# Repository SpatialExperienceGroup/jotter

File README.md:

# Jotter

## Requirements
- micro usb port for charging and for updating firmware
- 3.7V from a lipo battery
- lipo charging circuitry through a micro usb port
- bluetooth low energy beacon receiver and transmitter for positioning and ideally multilateration
- MCU to handle bluetooth beacon code
- accurate real time clock
- sd card for storing data; consider storing the unit id number on the sd card
- mems microphone on front for capturing talking of others
- mems microphone on the back for capturing talking of user
- MCU for DFT processing of the audio signals
- IrDA or similar for transmitting and receiving unique IDs to identify users facing users
- MCU to handing IrDA
- accelerometer to identify leaning and sitting
- pressure sensor to identify sitting and standing, usually these are only accurate to within 1 meter, which might not be good enough
- Wi-Fi capability for updating firmware, changing settings, and downloading data
- Any LEDs? charging, Wi-Fi transmission
- Any Buttons? Wi-Fi mode

---------------
## RTC
### DS3231*
- Arduino Library: Rtc by Makuna, Sodaq_DS3231

#### DS3231SN
- has temperature compensated crystal oscillator (may need this for cold temps)
- TCXO:Yes
- Alamrs:2
- $9.97@1, digi-key
- $6.59@100, digi-key
- $2.50@10, aliexpress

---------------
## Coin Cell Retainer/Holder
- Battery:CR2032
- Battery Diameter:20mm

### BU2032

#### BU2032-1-HD-G
- Type:through hole holder
- $0.83@1, digi-key
- $0.69@100, digi-key

#### BU2032SM-HD-G
- Type:surface mount holder
- $0.87@1, digi-key
- $0.76@100, digi-key

#### BK-912
- Type:surface mount retainer
- Notes:easy replacement
- $0.33@1, digi-key
- $0.29@100, digi-key

#### BK-913*
- Type:through hole retainer
- Notes:easy replacement
- $0.35@1, digi-key
- $0.30@100, digi-key

#### BK-888
- Type:through hole retainer
- blocks inner side
- easy replacement
- $0.39@1, digi-key
- $0.33@100, digi-key

---------------
## LDO
- Voltage 3.3V
- needed for running the esp8266 microprocessor and others
- ESP8266 typical
-- Modem-Sleep is 15mA with not much load
-- Wi-Fi Transmission could be up to 170mA, but it is unclear if this is an instantaneous load

### AMS1117-3.3**
- Package:SOT-223
- Current: 1100mA
- Input Voltage: Up to 6V
- Dropout Voltage: 1100mV@800mA
- $1.58@50, aliexpress

### SPX3819M5-L-3-3/TR**
- Package: SOT-23-5
- Current: 500mA
- Input Voltage: Up to 16V
- Dropout Voltage: 340mV@500mA
- $0.72@1, digi-key
- $0.49@100, digi-key

### MCP1700T-3302E/TT
- Package: SOT-23-3
- Current: 250mA
- Input Voltage: Up to 6V
- Dropout Voltage: 178mV@250mA
- $0.37@1, digi-key
- $0.28@100, digi-key

### TC1262-3.3VDBTR
- Package: SOT-223-3
- Current: 500mA
- Input Voltage: Up to 6V
- Dropout Voltage: 350mV@500mA
- $0.51@1, digi-key
- $0.39@100, digi-key

### MIC5528-3.3YMY-TR
- Package: 6-UFDFN (1.2x1.2)
- Current: 525mA
- Input Voltage: 2.5V to 5.5V
- $0.19@1, digi-key
- $0.14@100, digi-key

### NCP161AMX330TBG
- Package: 4-XDFN (1x1)
- Current: 450mA
- Input Voltage: 1.9V to 5.5V
- Dropout Voltage: 150mV@450mA
- $0.46@1, digi-key
- $0.22@100, digi-key

---------------
## LiPo Battery
- 3.7V

### 100mAh
- Weight: 3g
- Size: 11.5mm x 31 x 3.8mm / 0.45" x 1.2" x 0.15"
-   4mA@24hr
-  10mA@10hr
-  $5.95@1, Adafruit
-  $4.76@100, Adafruit

### 150mAh
- Weight: 4.65g
- Size: 19.75mm x 26.02mm x 3.8mm / 0.77" x 1.02" x 0.14"
-   6mA@24hr
-  15mA@10hr
-  $5.95@1, Adafruit
-  $4.76@100, Adafruit

### 350mAh
- Weight: 7.9g
- Size: 36mm x 20mm x 5.6mm / 1.4" x 0.8" x 0.22"
-  14mA@24hr
-  35mA@10hr
-  $6.95@1, Adafruit
-  $5.56@100, Adafruit

### 500mAh**
- Weight: 10.5g
- Size: 29mm x 36mm x 4.75mm / 1.15" x 1.4" x 0.19"
-- Little larger than a US Quarter
-  20mA@24hr
-  50mA@10hr
-  $7.95@1, Adafruit

### 1200mAh*
- Weight: 23g
- Size: 34mm x 62mm x 5mm / 1.3" x 2.4" x 0.2"
-  50mA@24hr
- 120mA@10hr
-  $9.95@1, Adafruit

### 2000mAh
- Weight: 34g
- Size: 60mm x 36mm x 7mm / 2.4" x 1.4" x 0.3"
-  83mA@24hr
- 200mA@10hr
- $12.50@1, Adafruit
- $10.00@100, Adafruit

### 2500mAh
- Weight: 52g
- Size: 2" x 2.55" x 0.30" (51mm x 65mm x 8mm)
- 104mA@24hr
- 250mA@10hr
- $14.95@1, Adafruit
- $11.96@100, Adafruit

---------------
## LiPo Charger

### MCP73831/2**
- Used by Adafruit
- Package: SOT-23-5
- Max Charge Current: 500mA
- Max Input Voltage: 6V
- $0.56@1, digi-key
- $0.42@100, digi-key

### MAX1555EZK+T
- Package: SOT-23-5
- Max Charge Current: 340mA
- Max Input Voltage: 7V
- $2.03@1, digi-key
- $1.34@100, digi-key

---------------
## MCU - Core

### ATSAMD11
- USB: Yes
- VCC: 1.62V - 3.63V
- Current Consumption Idle: 1.8mA
- Current Consumption While: 3mA
- Current Consumption CoreMark: 4mA
- Program Memory: 16KB
- CPU Frequency: 48MHz

#### ATSAMD11C
- SERCOM: 2

##### ATSAMD11C14A
- Package: 14-SOIC
- $2.32@1, digi-key
- $1.69@100, digi-key

#### ATSAMD11D
- SERCOM: 3

##### ATSAMD11D14A

###### ATSAMD11D14A-SSUT**
- Package: 20-SOIC
- $2.54@1, digi-key
- $1.85@100, digi-key

###### ATSAMD11D14A-MUT*
- Package: 24-QFN (4x4)
- $2.65@1, digi-key
- $1.93@100, digi-key

### ATSAMD21
- USB: Yes
- VCC: 1.62V - 3.63V
- Current Consumption Idle: 2.2mA
- Current Consumption While: 4mA
- Current Consumption CoreMark: 7mA
- Program Memory: 32/64/128/256KB
- CPU Frequency: 48MHz
- I2S: Yes

#### ATSAMD21E
- SERCOM:4
- ADC:10

##### ATSAMD21E18A
- Program Memory: 256KB

###### ATSAMD21E18A-MUT
- Package:32-VFQFN
- $5.30@1, digi-key
- $3.88@100, digi-key

###### ATSAMD21E15B-AUT
- Package:32-TQFP (7x7)
- $3.16@1, digi-key
- $2.32@100, digi-key

#### ATSAMD21G
- SERCOM:6
- ADC:14

#### ATSAMD21J
- SERCOM:6
- ADC:20

### LPGA
- Custom Reprogrammable Circuit Design

#### ICE40LP384-SG32
- Package: 32-QFN
- LABS/CLBs: 48
- Logic Elements: 384
- Dev Kit http://www.latticestore.com/searchresults/tabid/463/searchid/1/searchvalue/ice40hx1k-blink-evn/default.aspx
- $1.67@1, digi-key
- $1.38@100, digi-key

---------------
## MCU - IrDA, Bluetooth

### ATtiny85
- GCC Architecture: avr25
- Program Memory: 8KB
- TWI: 0
- SPI: 0
- USART: 0
- ADC: 4x10b

#### ATTINY85-20SU
- Package: 8-SOIC
- CPU Frequency: 20MHz
- $2.24@1, digi-key
- $1.63@100, digi-key

#### ATTINY85-20MUR
- Package: 20-QFN (4x4)
- CPU Frequency: 20MHz
- $2.08@1, digi-key
- $1.51@100, digi-key

### ATtiny841
- Program Memory: 8KB
- GCC Architecture: avr25
- CPU Frequency: 16MHz
- TWI: 1 Slave
- SPI: 1
- USART: 2

#### ATTINY841-SSUR**
- Package: 14-SOIC
- $2.11@1, digi-key
- $1.53@100, digi-key

#### ATTINY841-MUR*
- Package: 20-QFN (4x4)
- $2.16@1, digi-key
- $1.56@100, digi-key

#### ATTINY841-MMHR
- Package: 20-VQFN (3x3)
- $2.32@1, digi-key
- $1.68@100, digi-key

### ATtiny88
- Program Memory: 8KB
- GCC Architecture: avr25
- CPU Frequency: 12MHz
- TWI: 1
- SPI: 1
- USART: 0

#### ATTINY88-MU
- Package: 32-VQFN (5x5)
- $1.82@1, digi-key
- $1.32@100, digi-key

#### ATTINY88-AU
- Package: 32-TQFP (7x7)
- $1.96@1, digi-key
- $1.42@100, digi-key

### ATtiny40
- Program Memory: 4KB
- GCC Architecture: avrtiny10
- CPU Frequency: 12MHz
- TWI: 1 Slave
- SPI: 1
- USART: 0

#### ATTINY40-MMHR
- Package: 20-VQFN (3x3)
- $1.49@1, digi-key
- $1.09@100, digi-key

#### ATTINY40-XUR
- Package: 20-TSSOP
- $2.20@1, digi-key
- $1.60@100, digi-key

#### ATTINY40-SUR
- Package: 20-SOIC
- $2.14@1, digi-key
- $1.55@100, digi-key

### ATtiny828
- Program Memory: 8KB
- GCC Architecture: avr25
- CPU Frequency: 20MHz
- TWI: 1 Slave
- SPI: 1
- USART: 1

#### ATTINY828-AUR
- Package: 32-TQFP (7x7)
- $2.45@1, digi-key
- $1.78@100, digi-key

#### ATTINY828-MUR
- Package: 32-VQFN (5x5)
- $2.67@1, digi-key
- $1.94@100, digi-key

---------------
## MEMS Microphones
- I2S digital input type
- Sensitivity: http://www.analog.com/en/analog-dialogue/articles/understanding-microphone-sensitivity.html
-- In near-field applications, such as cell phones, where the microphone is close to the sound source, a microphone with higher sensitivity is more likely to reach the maximum acoustic input, clip, and cause distortion. On the other hand, a higher sensitivity may be desirable in far-field applications, such as conference phones and security cameras, where the sound is attenuated as the distance from the source to the microphone increases.
-- Normal Conversation at 1m is around 63dB SPL

### SPH0645LM4H-B*
- Port: Bottom
- Frequency Range: 20Hz to 20kHz
- Sensitivity: -26dB ±3dB @ 94dB SPL
- SNR: 65dB(A)
- Supply Volgage: 1.62V to 1.8V to 3.6V
- Supply Current: 0.6mA
- Precision: 18-bit (6 additional bits are zeros, making 24-bit total)
- $3.06@1, digi-key
- $2.29@1, mouser
- $1.90@100, digi-key
- $1.51@100, mouser

### ICS-43432
- Port: Bottom
- Frequency Range: 50Hz to 20kHz
- Sensitivity: -26dB ±1dB @ 94dB SPL
- SNR: 65dB(A)
- Supply Volgage: 1.62V to 1.8V to 3.6V
- Supply Current: 1.5mA
- Precision: 24-bit
- $3.18@1, digi-key
- $2.15@100, digi-key
- example circuit: https://www.tindie.com/products/onehorse/ics43432-i2s-digital-microphone/
- Library: https://github.com/nodae/teensy_i2s_experimental

### INMP441ACEZ-R7
- Port: Bottom
- Frequency Range: 60Hz to 15kHz
- Sensitivity: -26dB ±3dB @ 94dB SPL
- SNR: 61dB(A)
- Supply Volgage: 1.62V to 1.8V to 3.6V
- Supply Current: 1.6mA
- Precision: 24-bit
- $4.35@1, digi-key
- $3.14@100, digi-key

### SPU0414HR5H
- Output Type: Analog
- Port: Top
- Frequency Range: 100Hz to 10kHz
- Sensitivity: -22dB ±3dB @ 94dB SPL
- SNR: 59dB(A)
- Supply Volgage: 1.5V to 3.6V
- Supply Current: 0.22mA
- $2.01@1, digi-key
- $1.10@100, digi-key
- $1.87@1, mouser
- $1.03@100, mouser

### SPW2430HR5H-B
- Output Type: Analog
- Port: Top
- Frequency Range: 100Hz to 10kHz
- Sensitivity: -42dB ±3dB @ 94dB SPL (not good)
- SNR: 59dB(A)
- Supply Volgage: 1.5V to 3.6V
- Supply Current: 0.11mA
- $1.11@1, digi-key
- $0.60@100, digi-key
- $1.04@1, mouser
- $0.59@100, mouser

## MCU - DFT Audio Signal Processor
- Interface: I2S

### ESP8266*
- Wi-Fi:Yes
- Allows us to have a Wi-Fi interface for setting the time and other settings.
- VCC:3.3V
- Runs on 3.3V, so should have an LDO or similar to bring down the 5V supply.
- pin mapping: http://www.esp8266.com/wiki/doku.php?id=esp8266_gpio_pin_allocations
- Has I2S inputs for digital audio of Left and Right microphones
- Peak Current Consumption on Startup: 320mA (use 470uF SMD)
- Current Consumption Idle: 15mA
- Current Consumption Wi-Fi Receive: 70mA
- Current Consumption Wi-Fi Transmit: <170mA
- I2S Forum: http://www.esp8266.com/viewtopic.php?f=13&t=7404
- I2S Example Code: https://github.com/cnlohr/esp8266duplexi2s
- DFT Example Code: https://github.com/cnlohr/channel3

### ATSAMD21

#### ATSAMD21E18A-MUT
- Package:32-VFQFN
- $5.30@1, digi-key
- $3.88@100, digi-key

#### ATSAMD21E15B-AUT
- Package:32-TQFP (7x7)
- $3.16@1, digi-key
- $2.32@100, digi-key

---------------
## IrDA Transciever
- http://www.societyofrobots.com/electronics_irda_tutorial.shtml
- Modulation Frequency: 38KHz
- most single packages are expensive, so we split into two parts
- may need to offload processing to small chip like Attiny85

### IrDA Sensor Pair

### IrDA Processor
- Encoder/Decoder

#### ATtiny MCU

#### MCP2155

#### MCP2122

### IrDA Receiver

#### VS1838B

#### TSOP38238

#### TSOP4038

#### TSOP4838

#### HS0038B

#### TSOP58238

#### TSOP6238TR

#### TSMP77000TT
- Distance: 5m
- Voltage Supply: 2.5V to 5.5V
- $1.66@1, digi-key
- $1.21@100, digi-key

### IrDA Transmitter
- Can be controlled with a 555 timer or an MCU

#### ATtiny MCU

#### NE555
- Supply Voltage: Typically 5V operation
- Max Frequency: 1MHz

#### TLC555
- Supply Voltage: 2V-15V
- Temperature Range: 0C to +70C
- Package: 8-SOIC
- Max Frequency: 2.1MHz
- $0.72@1, digi-key
- $0.48@100, digi-key

#### ICM7555
- Supply Voltage: 2V-18V
- Drop in replacement for NE555
- Max Frequency: 1MHz

##### ICM7555CBAZ
- Package: 8-SOIC
- Temperature Range: 0C to +70C
- $0.73@1, digi-key
- $0.50@100, digi-key

##### ICM7555IBAZ
- Package: 8-SOIC
- Temperature Range: -25C to +85C
- $0.73@1, digi-key
- $0.50@100, digi-key

---------------
## IMU
- need to detect sitting vs standing
- may include accelerometer, gyro, barometer, and perhaps magnetometer; why not

### MPU9250
- DoF:9

---------------
## Environmental Sensor

### BMP280

---------------
## Bluetooth Module for Beacon

### nRF24L01+*
- Chipset: nRF24L01
- FCC Certified: No

### MDBT40P**
- Chipset:nrf51822
- FCC Certified: Yes, SH6MDBT40

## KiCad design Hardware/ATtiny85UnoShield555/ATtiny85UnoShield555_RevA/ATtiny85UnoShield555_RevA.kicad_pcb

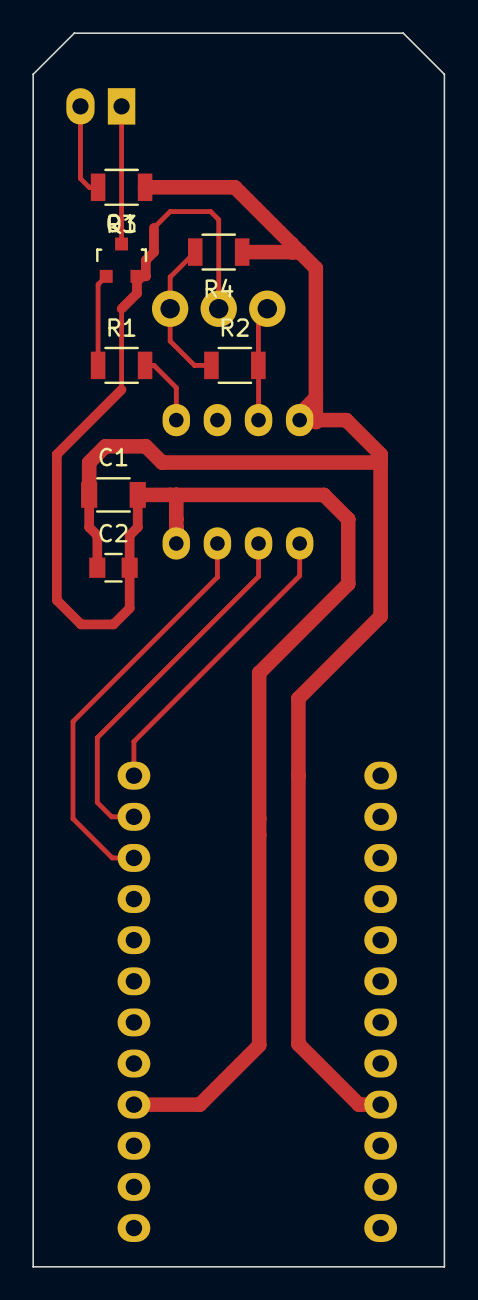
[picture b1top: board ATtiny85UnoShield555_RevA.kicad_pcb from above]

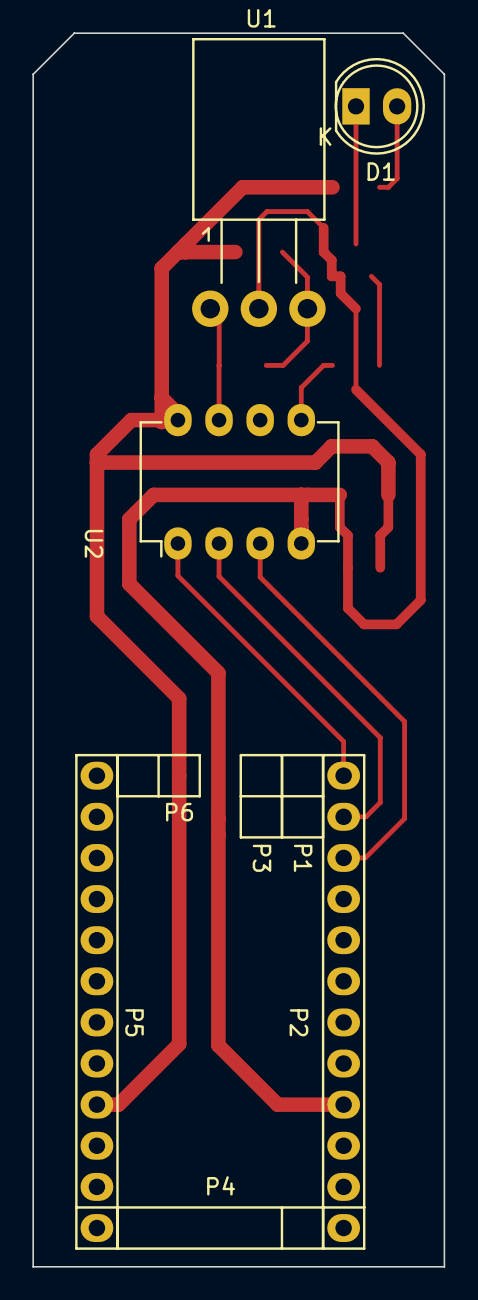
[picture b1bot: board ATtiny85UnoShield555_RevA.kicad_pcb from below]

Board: 2 copper layers, 25.4 x 76.2 mm, 16 parts (9 on the bottom side), 12 nets.

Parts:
C1: 10uF; C_1206
C2: 0.1uF; C_0805
D1: LED; LED-5MM
P1, P3: ADC; Socket_Strip_Arduino_1x02
P2: Digital; Socket_Strip_Arduino_1x12
P4: COM; Socket_Strip_Arduino_1x05
P5: Analog; Socket_Strip_Arduino_1x12
P6: PWR; Socket_Strip_Arduino_1x02
Q1: BSS138; SOT-23
R1: 1K; R_1206
R2: 10K; R_1206
R3: 10; R_1206
R4: 47; R_1206
U1: TSOP382xx; SOT126_SOT32_Housing_Horizontal
U2: ATTINY85-20PU; DIP-8_W7.62mm

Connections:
/Reset: P2.3, P5.3
FROM_IR_RECEIVER: R2.2, U1.1, U2.7
GND: C1.2, C2.2, P2.4, P5.2, Q1.2, U1.2, U2.4
unnamed: D1.1, Q1.3
unnamed: D1.2, R3.2
unnamed: Q1.1, R1.1
unnamed: R2.1, R4.2, U1.3
TINY_RESET: P2.12, U2.1
TO_IR_TRANSMITTER: R1.2, U2.5
TX_TO_MCU: P2.10, U2.3
TX_TO_TINY: P2.11, U2.2
V33: C1.1, C2.1, P5.4, R3.1, R4.1, U2.8

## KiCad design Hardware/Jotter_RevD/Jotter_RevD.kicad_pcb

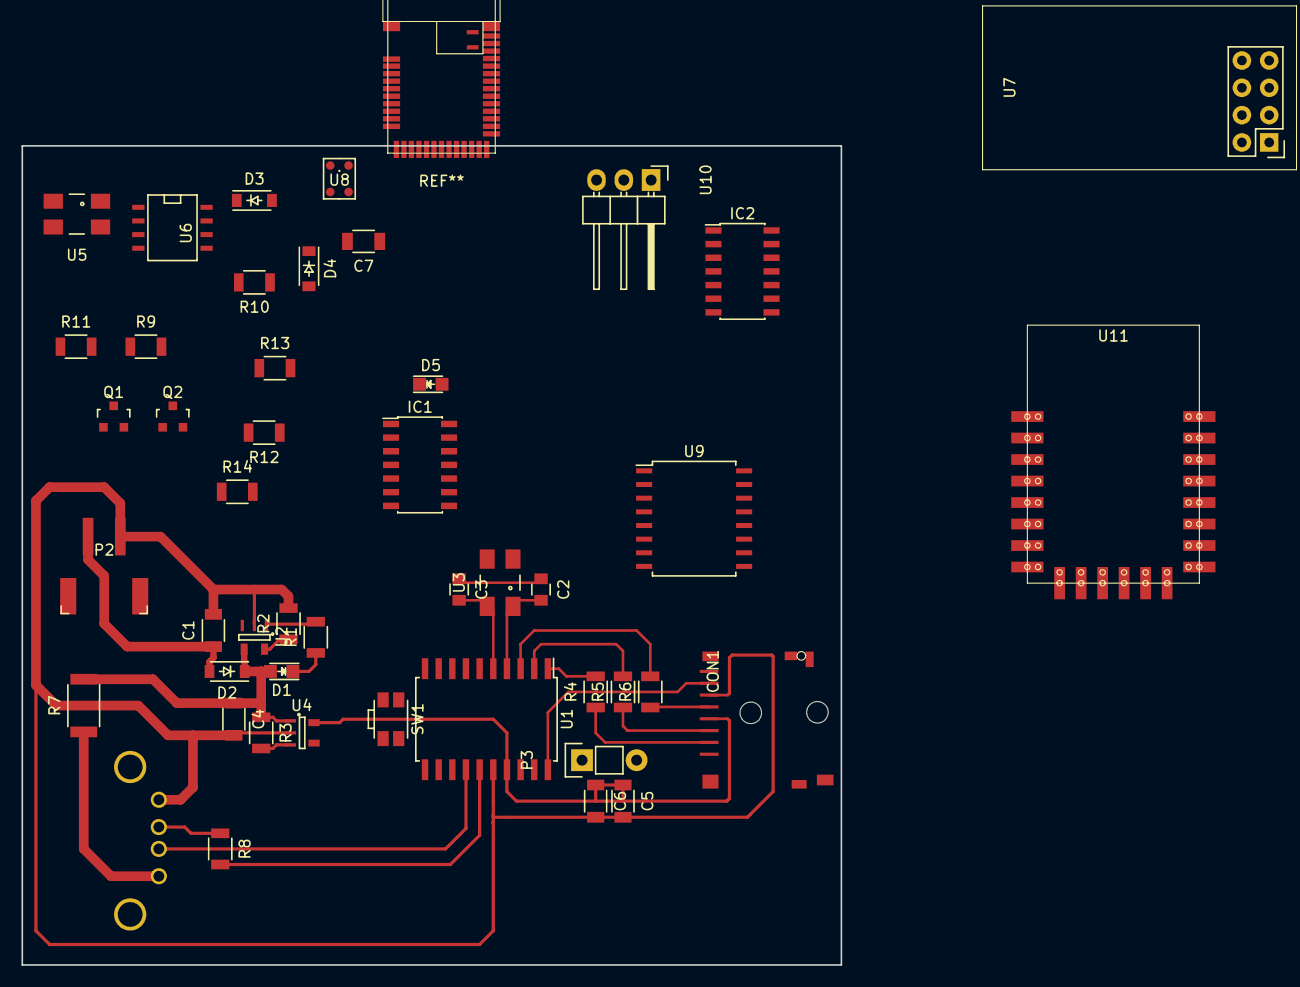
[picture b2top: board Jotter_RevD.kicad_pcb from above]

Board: 2 copper layers, 76.2 x 76.2 mm, 46 parts (1 on the bottom side), 34 nets.

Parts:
C1, C4, C5: 10uF; C_1206
C2, C3: C; C_0805
C6: 1uF; C_1206
C7: 2.2uF; C_1206
CON1: SD_Card; DM3D-SF-80
D1, D5: LED; LED-0805
D2, D3, D4: D_Schottky; SOD-123
IC1, IC2: ATTINY841-SSU; SOIC-14_3.9x8.7mm_Pitch1.27mm
P1: USB_A
P2: CONN_01X02; JST-S2B-PH-SM4
P3: CONN_01X02; Pin_Header_Straight_1x02
Q1, Q2: BSS138; SOT-23
R1, R12, R14: 1K; R_1206
R2, R9, R10, R11, R13: 10K; R_1206
R3: 100K; R_1206
R4, R5, R6, R8: 0; R_1206
R7: 0; R_2010
SW1: SPST; SW_SPST_EVQP7A
U1: ATSAMD11D14A; SOIC-20_7.5x12.8mm_Pitch1.27mm
U2: MCP73831; SOT-23-5-80
U3, U5: ABS25; Crystal_SMD_0603_4Pads
U4: SPX3819; SOT-23-5-80
U6: PCF8563T; SO-08-N-80
U7: NRF24L01+
U8: SPU0414HR5H; SPU0414HR5H-SB
U9: DS3231; SOIC-16-W-80
U10: VS18388; Pin_Header_Angled_1x03
U11: ESP8266-12E; ESP8266-12E-80

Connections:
3V3: C5.1, C6.1, CON1.4, D3.2, P3.2, Q1.1, Q2.1, R9.1, R10.1, R11.1, R13.1, U1.17, U4.5, U8.1
APA_CLK: Q2.3, R14.2
APA_DATA: Q1.3, R12.2
Buzzer: P3.1, U1.18
GND: C1.2, C2.1, C3.1, C4.2, C5.2, C6.2, C7.2, CON1.6, P1.4, P2.1, R2.2, SW1.2, U1.16, U2.2, U4.2, U6.4, U8.2
I2C_SCL: R9.2, U1.10, U6.6
I2C_SDA: R10.2, U1.9, U6.5
MEMS: U1.6, U8.4
unnamed: C7.1, U8.3
unnamed: CON1.2, R4.1
unnamed: CON1.3, R5.1
unnamed: CON1.5, R6.1
unnamed: D1.1, R1.1
unnamed: D3.1, D4.1, U6.8
unnamed: P1.1, R7.1
unnamed: P1.3, R8.1
unnamed: R1.2, U2.1
unnamed: R2.1, U2.5
unnamed: R3.2, U4.3
unnamed: U5.1, U6.1
unnamed: U5.4, U6.2
PIN_15: Q2.2, R13.2, U1.7
PIN_16: Q1.2, R11.2, U1.8
RESET: SW1.1, U1.11
SPI_MISO: CON1.7, U1.20
SPI_MOSI: R5.2, U1.2
SPI_SCK: R6.2, U1.3
SPI_SS: R4.2, U1.1
USB+: R8.2, U1.15
USB-: P1.2, U1.14
V_BAT: C1.1, D2.2, P2.2
V_USB: C4.1, D1.2, D2.1, R3.1, R7.2, R12.1, R14.1, U2.4, U4.1
XIN: C2.2, U1.4, U3.1
XOUT: C3.2, U1.5, U3.4

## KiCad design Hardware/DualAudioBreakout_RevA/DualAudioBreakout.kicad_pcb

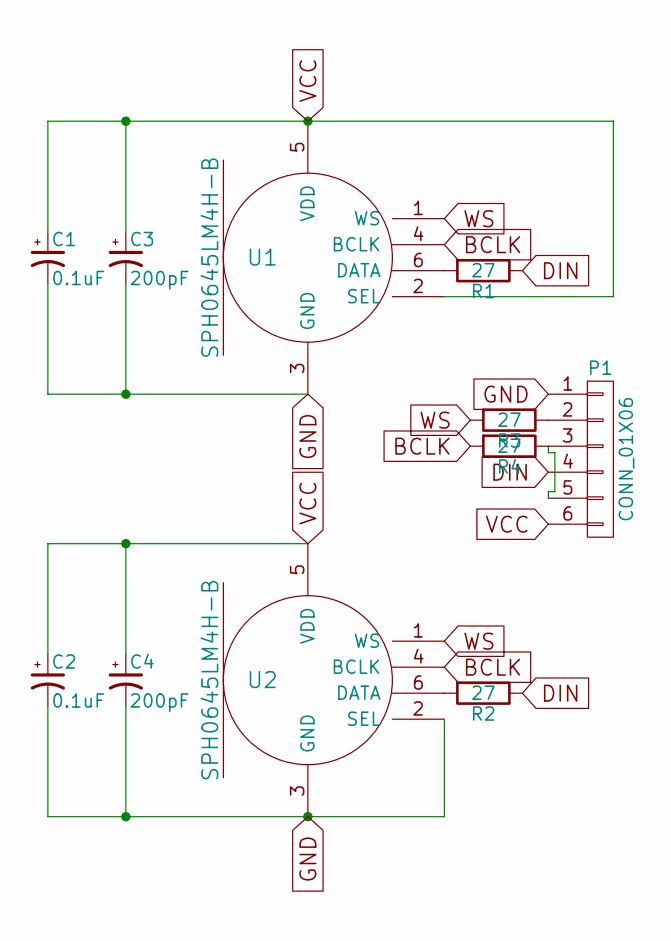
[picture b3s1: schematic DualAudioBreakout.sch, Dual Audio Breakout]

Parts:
C1, C2: 0.1uF; C_0805
C3, C4: 200pF; C_0805
P1: CONN_01X06; Pin_Header_Straight_1x06
R1, R2, R3, R4: 27; R_0805
U1, U2: SPH0645LM4H-B

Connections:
BCLK: R4.2, U1.4 (BCLK), U2.4 (BCLK)
DIN: P1.4, R1.1, R2.1
GND: C1.2, C2.2, C3.2, C4.2, P1.1, U1.3 (GND), U2.2 (SEL), U2.3 (GND)
unnamed: P1.2, R3.1
unnamed: P1.3, P1.5, R4.1
unnamed: R1.2, U1.6 (DATA)
unnamed: R2.2, U2.6 (DATA)
VCC: C1.1, C2.1, C3.1, C4.1, P1.6, U1.2 (SEL), U1.5 (VDD), U2.5 (VDD)
WS: R3.2, U1.1 (WS), U2.1 (WS)

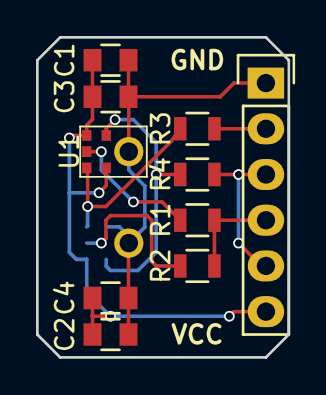
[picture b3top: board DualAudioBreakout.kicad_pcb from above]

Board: 2 copper layers, 14.0 x 17.8 mm, 11 parts (1 on the bottom side), 9 nets.

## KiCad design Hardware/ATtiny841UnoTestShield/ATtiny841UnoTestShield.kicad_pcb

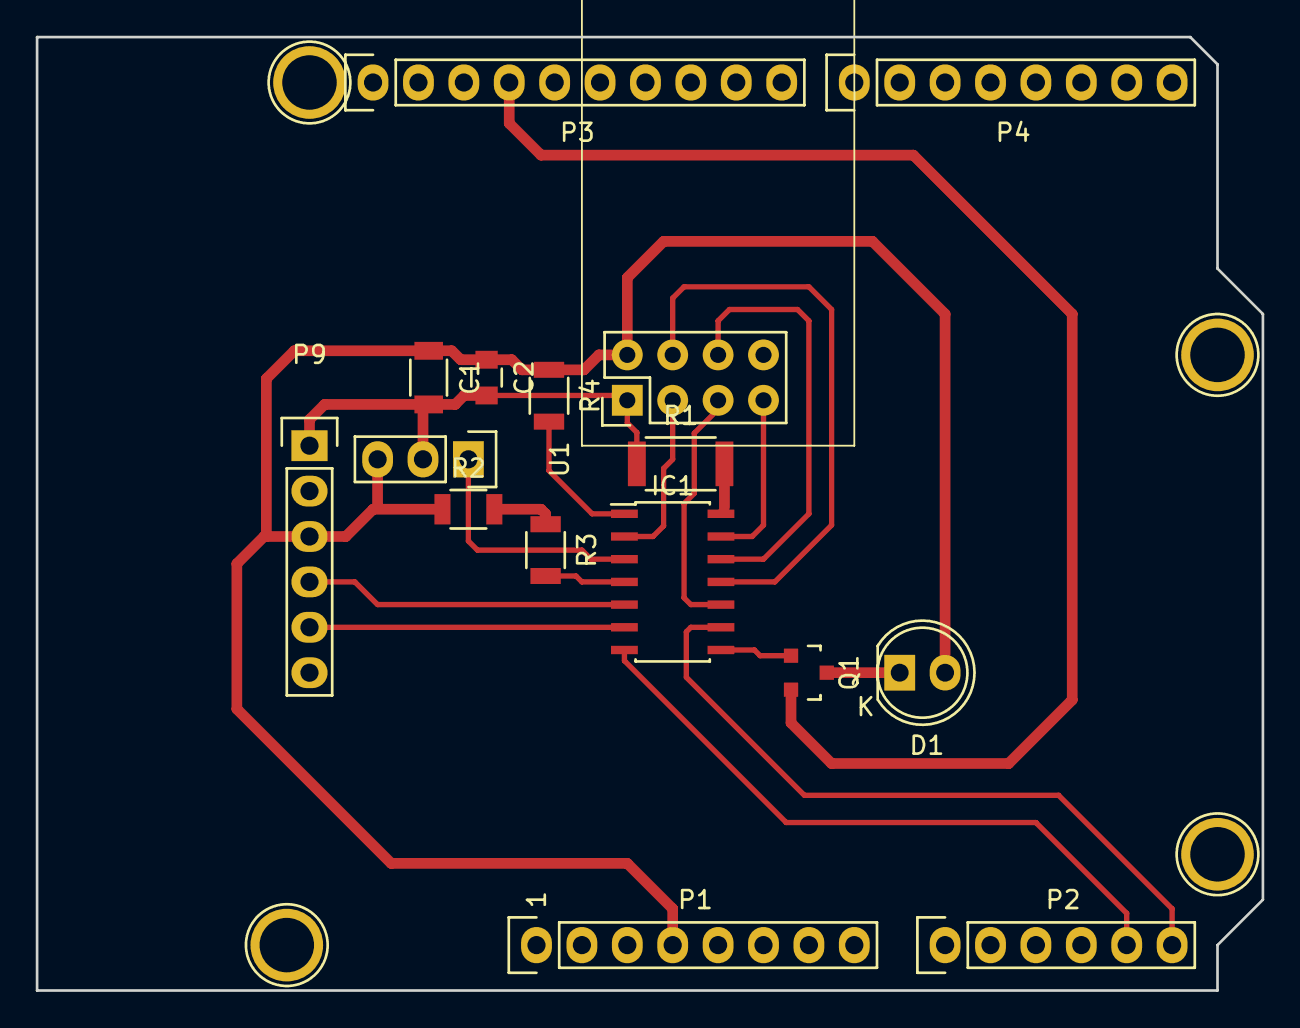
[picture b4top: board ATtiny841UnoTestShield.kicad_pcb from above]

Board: 2 copper layers, 68.6 x 53.3 mm, 20 parts (0 on the bottom side), 16 nets.

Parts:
C1: 10uF; C_1206
C2: 0.1uF; C_0805
D1: LED; LED-5MM
IC1: ATTINY841-SSU; SOIC-14-N-80
P1: Power; Socket_Strip_Arduino_1x08
P2: Analog; Socket_Strip_Arduino_1x06
P3: Digital; Socket_Strip_Arduino_1x10
P4: Digital; Socket_Strip_Arduino_1x08
P5, P6, P7, P8: CONN_01X01; Arduino_1pin
P9: FTDI; Pin_Header_Straight_1x06
Q1: BSS138; SOT-23
R1: 0; R_2010
R2, R4: 0; R_1206
R3: 10K; R_1206
U1: VS18388; Pin_Header_Straight_1x03
U2: NRF24L01+

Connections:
CE: IC1.2, U2.3
GND: C1.2, C2.2, IC1.14, P1.6, P1.7, P3.4, P9.1, Q1.2, R1.1, R1.2, U1.2, U2.1
IRINPUT: IC1.3, U1.1
IRLED: IC1.8, Q1.1
MISO_ALT: IC1.13, U2.7
MOSI_ALT: IC1.12, U2.6
unnamed: D1.1, Q1.3
unnamed: IC1.4, R3.2
unnamed: R2.2, R3.1
RXI: IC1.6, P9.5
SCK_ALT: IC1.10, U2.5
SCL: IC1.9, P2.6, P3.1
SDA: IC1.7, P2.5, P3.2
SS_ALT: IC1.11, U2.4
TXO: IC1.5, P9.4
V33: C1.1, C2.1, D1.2, IC1.1, P1.4, P9.3, R2.1, R4.1, R4.2, U1.3, U2.2

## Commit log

2016-10-16 added all prexisting files to repo
2016-10-16 added notes on parts to the readme
2016-10-17 added notes on which parts to select for development; added rought shematic and layout with most selected parts on the 3in by 3in layout to get a sense of component sizes.
2016-10-17 corrected markdown in readme for better legibility
2016-11-30 added hardware design for 841 uno shield with ir and ble
2017-05-10 added IR transciever circuit for IR testing
